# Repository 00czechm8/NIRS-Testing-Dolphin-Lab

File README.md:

# Thermistor Documentation

## Background
This project is meant to provide scientific backing for a change to the NIRS system so that it does not cause any burns to the Dolphins. NIRS is a system that uses LED light sources to bounce photons off tissue to determine concentrations of specific molecules in the subject's bloodstream. Although the current system returns excellent results, the system causes burns on the subject's skin. Therefore we attempt to quantify the burn damage to the dolphin skin and create a design solution that minimizes damage. 

# Test Setup Design
Given the simplicity of the design, we opted for a simple circuit where a thermistor was placed in series with a 10-kilohm resistor (with voltage being dropped across the thermistor first). Using a teensy 4.0, we would measure the voltage across the resistor and thus achieve a direct relationship between temperature and pressure. 

# Voltage to Temperature Reading
According to the literature[1], we can create an accurate fit using a quartic polynomial from the ratio of the thermistor resistance to the 10-kilohm resistor and the reciprocal of temperature. 

## Calibration Curves and Residuals

## Calibration Data
This data can be found in the Code directory of the main branch

## References
[1]: S. Rudtsch and C. von Rohden, “Calibration and self-validation of thermistors for high- 
       precision temperature measurements,” Measurement, vol. 76, pp. 1–6, Dec. 2015. 
       doi:10.1016/j.measurement.2015.07.028.

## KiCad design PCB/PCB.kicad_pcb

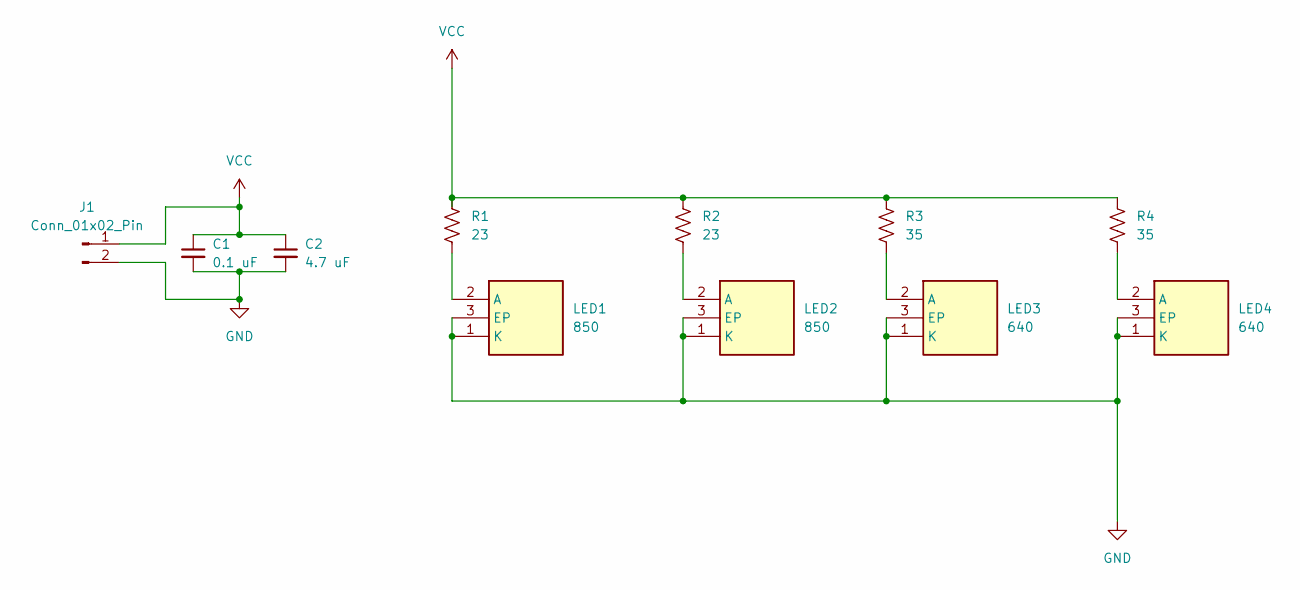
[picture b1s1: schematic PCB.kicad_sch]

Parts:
C1: 0.1 uF; C_0402_1005Metric_Pad0.74x0.62mm_HandSolder
C2: 4.7 uF; C_0402_1005Metric_Pad0.74x0.62mm_HandSolder
J1: Conn_01x02_Pin; PinSocket_1x02_P2.54mm_Vertical
LED1, LED2: 850; SST10IRB90K85000; Mouser Part Number 896-SST10IRB90K85000
LED3, LED4: 640; SST10IRB90K85000; Mouser Part Number 896-SST10IRB90K85000
R1, R2: 23; R_Axial_DIN0614_L14.3mm_D5.7mm_P25.40mm_Horizontal
R3, R4: 35; R_Axial_DIN0614_L14.3mm_D5.7mm_P25.40mm_Horizontal

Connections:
GND: C1.2, C2.2, J1.2, LED1.1 (K), LED1.3 (EP), LED2.1 (K), LED2.3 (EP), LED3.1 (K), LED3.3 (EP), LED4.1 (K), LED4.3 (EP)
unnamed: LED1.2 (A), R1.2
unnamed: LED2.2 (A), R2.2
unnamed: LED3.2 (A), R3.2
unnamed: LED4.2 (A), R4.2
VCC: C1.1, C2.1, J1.1, R1.1, R2.1, R3.1, R4.1

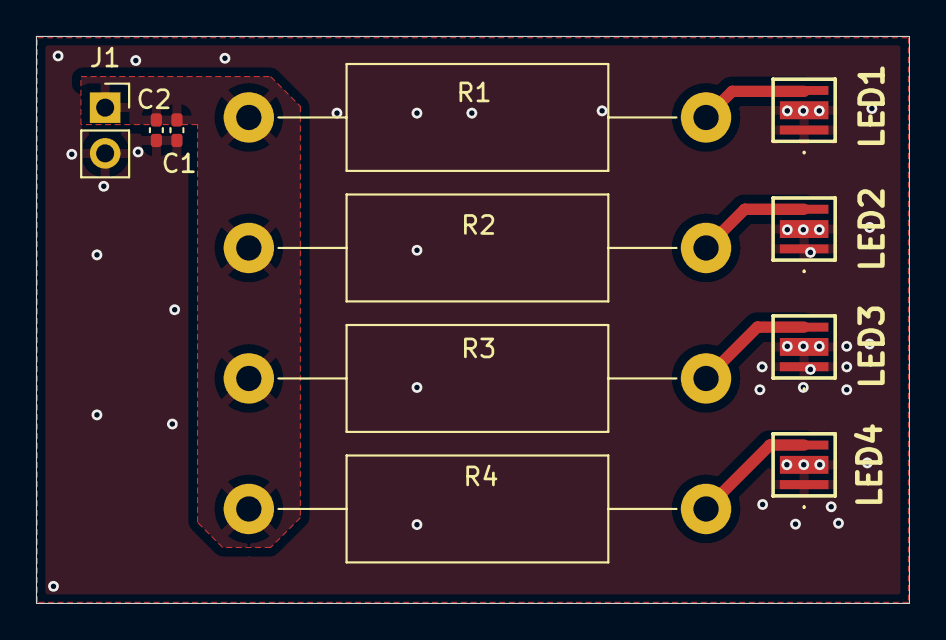
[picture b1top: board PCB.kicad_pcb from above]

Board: 2 copper layers, 48.5 x 31.5 mm, 11 parts (0 on the bottom side), 6 nets.

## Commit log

2024-05-24 dkfjdkfj
2024-05-24 Cleaning House
2024-05-24 Adding dummy text file
2024-05-24 Correcting Issue with original CAD files
2024-05-24 Adding Plots and Raw Data Table
2024-05-24 Adding Arduino Thermistor Code
2024-05-24 Arduino tings
2024-05-24 Arduino knows where it can put itself
2024-05-24 Working Arduino code for temperture
2024-05-30 Added a bunch
2024-05-30 forgot to save these just now
2024-05-30 added temp curves and inital OD curves
2024-07-11 Long overdo update.
    Overview:
    -Switched from Seinhart fit to lookup table and linear regression for temp sensors
    -Ran temperature tests for pla shims, tough 1500 shims, aluminum shims, and silicone shims
    -Ran optical trials for PLA and Tough 1500 Shims using the Oxy2MAT converter and the Oxy2ODGraph files
    -Created PCB for SM LEDs with wavelenghts of 740 and 850 nm according to Artinis documentation
    -Created mount to test Artinis LED board with BIVAR polycarbonate light pipes and saw no meaningful results
2024-07-12 Updating an image and some code
